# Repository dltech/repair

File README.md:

# repair
* DT9205 DMM schematic and label stickers

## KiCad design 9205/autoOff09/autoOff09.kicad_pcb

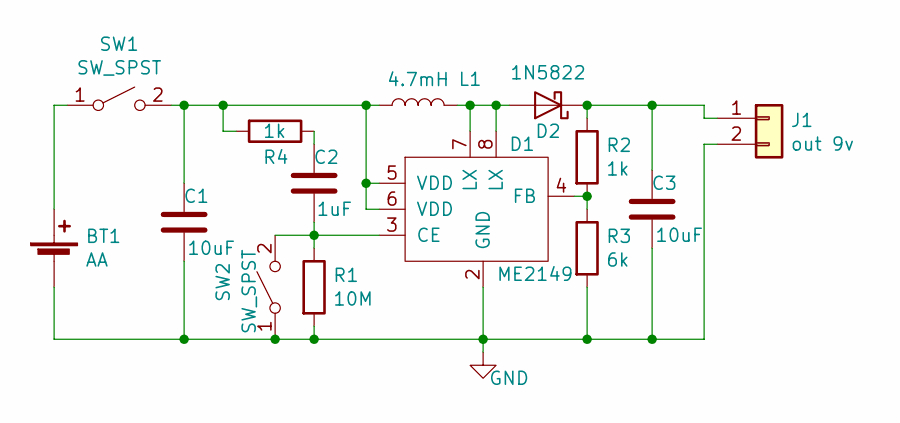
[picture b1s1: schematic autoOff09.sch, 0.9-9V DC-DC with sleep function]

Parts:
BT1: AA; D_SMB_Handsoldering
C1, C3: 10uF; C_0805_2012Metric
C2: 1uF; C_0805_2012Metric
D1: ME2149; SO-8_3.9x4.9mm_P1.27mm
D2: 1N5822; D_SMA
J1: out 9v; D_SMB_Handsoldering
L1: 4.7mH; L_7.3x7.3_H4.5
R1: 10M; R_0805_2012Metric
R2, R4: 1k; R_0805_2012Metric
R3: 6k; R_0805_2012Metric
SW1, SW2: SW_SPST; D_SMB_Handsoldering

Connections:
GND: BT1.2 (-), C1.1, C3.1, D1.1, D1.2 (GND), J1.2, R1.2, R3.2, SW2.1 (A)
unnamed: BT1.1 (+), SW1.1 (A)
unnamed: C1.2, D1.5 (VDD), D1.6 (VDD), L1.1, R4.2, SW1.2 (B)
unnamed: C2.1, D1.3 (CE), R1.1, SW2.2 (B)
unnamed: C2.2, R4.1
unnamed: C3.2, D2.1 (K), J1.1, R2.1
unnamed: D1.4 (FB), R2.2, R3.1
unnamed: D1.7 (LX), D1.8 (LX), D2.2 (A), L1.2

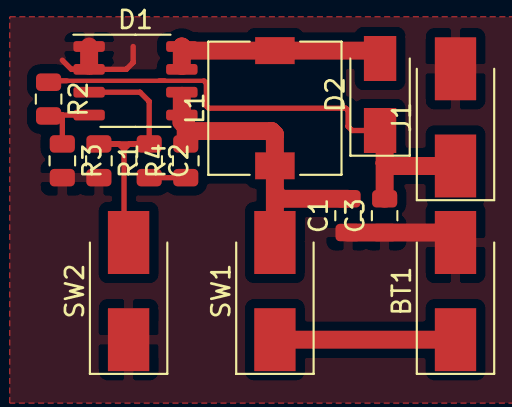
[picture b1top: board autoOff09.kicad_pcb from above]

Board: 2 copper layers, 14 parts (0 on the bottom side), 8 nets.

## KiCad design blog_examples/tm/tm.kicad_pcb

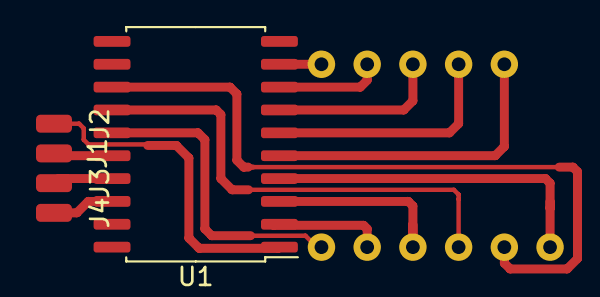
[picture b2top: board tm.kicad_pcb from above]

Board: 2 copper layers, 6 parts (1 on the bottom side), 15 nets.

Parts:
D1: LED_3digit; FYT-3631_nonc
J1: VCC; SolderWirePad_1x01_SMD_1x2mm
J2: GND; SolderWirePad_1x01_SMD_1x2mm
J3: CLK; SolderWirePad_1x01_SMD_1x2mm
J4: DIO; SolderWirePad_1x01_SMD_1x2mm
U1: TM1637; SOIC-20W_7.5x12.8mm_P1.27mm

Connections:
+3V3: J1.1, U1.16
GND: J2.1, U1.1
unnamed: D1.1, U1.9
unnamed: D1.2, U1.8
unnamed: D1.3, U1.7
unnamed: D1.4, U1.6
unnamed: D1.5, U1.5
unnamed: D1.7, U1.4
unnamed: D1.8, U1.13
unnamed: D1.9, U1.14
unnamed: D1.10, U1.3
unnamed: D1.11, U1.2
unnamed: D1.12, U1.15
unnamed: J3.1, U1.17
unnamed: J4.1, U1.18

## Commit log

2021-03-20 paint labels
2021-03-20 shchematic for single battery supply
2021-07-18 new example for blog
2022-04-15 IR remote loger
2022-04-16 ir remote loger OK
2022-04-16 nec decoder
2022-04-16 samsung decoder
2022-04-18 ir receiver ok
2022-04-30 lukey
2022-08-09 updated ubuntu softkit
2022-11-28 dc-dc example
